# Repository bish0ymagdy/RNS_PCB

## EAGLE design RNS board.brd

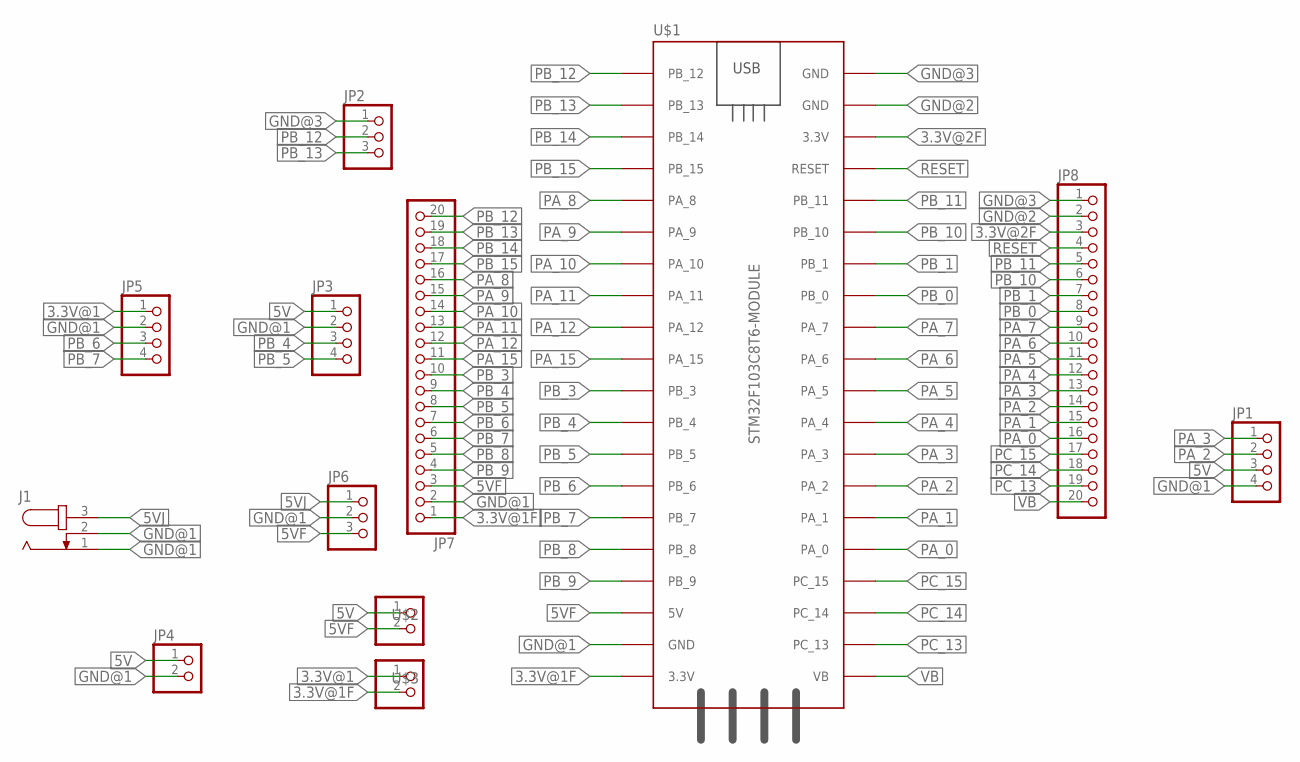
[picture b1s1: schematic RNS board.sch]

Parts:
J1: JACK-PLUG0; SPC4077
JP1, JP3, JP5: PINHD-1X4; 1X04
JP2, JP6: PINHD-1X3; 1X03
JP4: PINHD-1X2; 1X02
JP7, JP8: PINHD-1X20; 1X20
U$1: STM32F103C8T6-MODULE
U$2, U$3: PINHD-1X2; 1X02

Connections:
3.3V@1: JP5.1, U$3.1
3.3V@1F: JP7.1, U$1.3.3V_1 (3.3V), U$3.2
3.3V@2F: JP8.3, U$1.3.3V_2 (3.3V)
5V: JP1.3, JP3.1, JP4.1, U$2.1
5VF: JP6.3, JP7.3, U$1.5V, U$2.2
5VJ: J1.3, JP6.1
GND@1: J1.1, J1.2, JP1.4, JP3.2, JP4.2, JP5.2, JP6.2, JP7.2, U$1.GND_1 (GND)
GND@2: JP8.2, U$1.GND_2 (GND)
GND@3: JP2.1, JP8.1, U$1.GND_3 (GND)
PA_0: JP8.16, U$1.PA_0
PA_1: JP8.15, U$1.PA_1
PA_2: JP1.2, JP8.14, U$1.PA_2
PA_3: JP1.1, JP8.13, U$1.PA_3
PA_4: JP8.12, U$1.PA_4
PA_5: JP8.11, U$1.PA_5
PA_6: JP8.10, U$1.PA_6
PA_7: JP8.9, U$1.PA_7
PA_8: JP7.16, U$1.PA_8
PA_9: JP7.15, U$1.PA_9
PA_10: JP7.14, U$1.PA_10
PA_11: JP7.13, U$1.PA_11
PA_12: JP7.12, U$1.PA_12
PA_15: JP7.11, U$1.PA_15
PB_0: JP8.8, U$1.PB_0
PB_1: JP8.7, U$1.PB_1
PB_3: JP7.10, U$1.PB_3
PB_4: JP3.3, JP7.9, U$1.PB_4
PB_5: JP3.4, JP7.8, U$1.PB_5
PB_6: JP5.3, JP7.7, U$1.PB_6
PB_7: JP5.4, JP7.6, U$1.PB_7
PB_8: JP7.5, U$1.PB_8
PB_9: JP7.4, U$1.PB_9
PB_10: JP8.6, U$1.PB_10
PB_11: JP8.5, U$1.PB_11
PB_12: JP2.2, JP7.20, U$1.PB_12
PB_13: JP2.3, JP7.19, U$1.PB_13
PB_14: JP7.18, U$1.PB_14
PB_15: JP7.17, U$1.PB_15
PC_13: JP8.19, U$1.PC_13
PC_14: JP8.18, U$1.PC_14
PC_15: JP8.17, U$1.PC_15
RESET: JP8.4, U$1.RESET
VB: JP8.20, U$1.VB

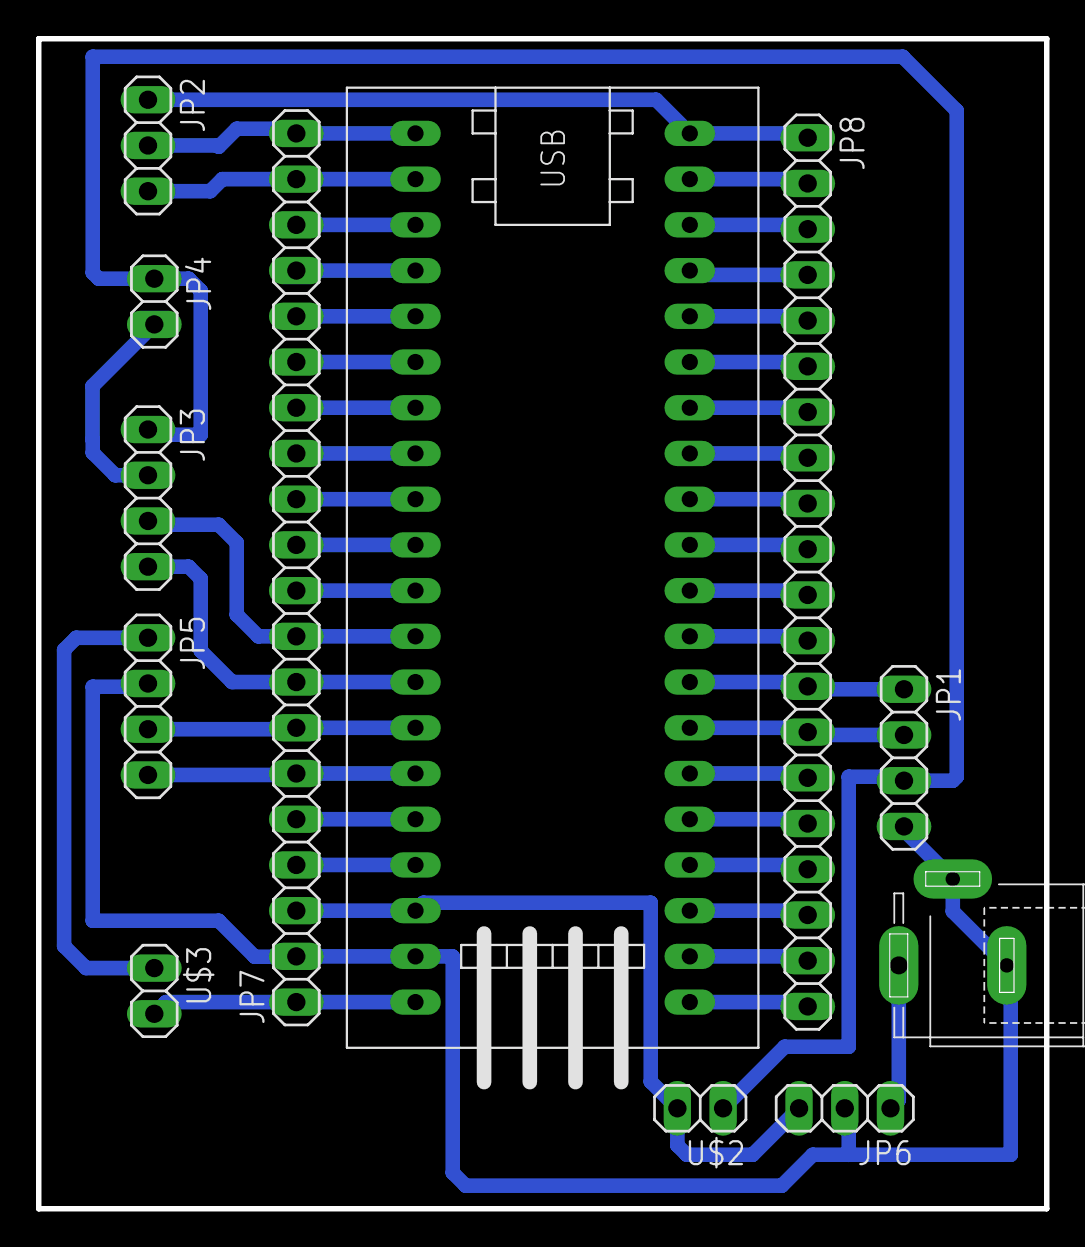
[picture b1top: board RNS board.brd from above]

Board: 2 copper layers, 56.0 x 65.0 mm, 12 parts (0 on the bottom side), 43 nets.
